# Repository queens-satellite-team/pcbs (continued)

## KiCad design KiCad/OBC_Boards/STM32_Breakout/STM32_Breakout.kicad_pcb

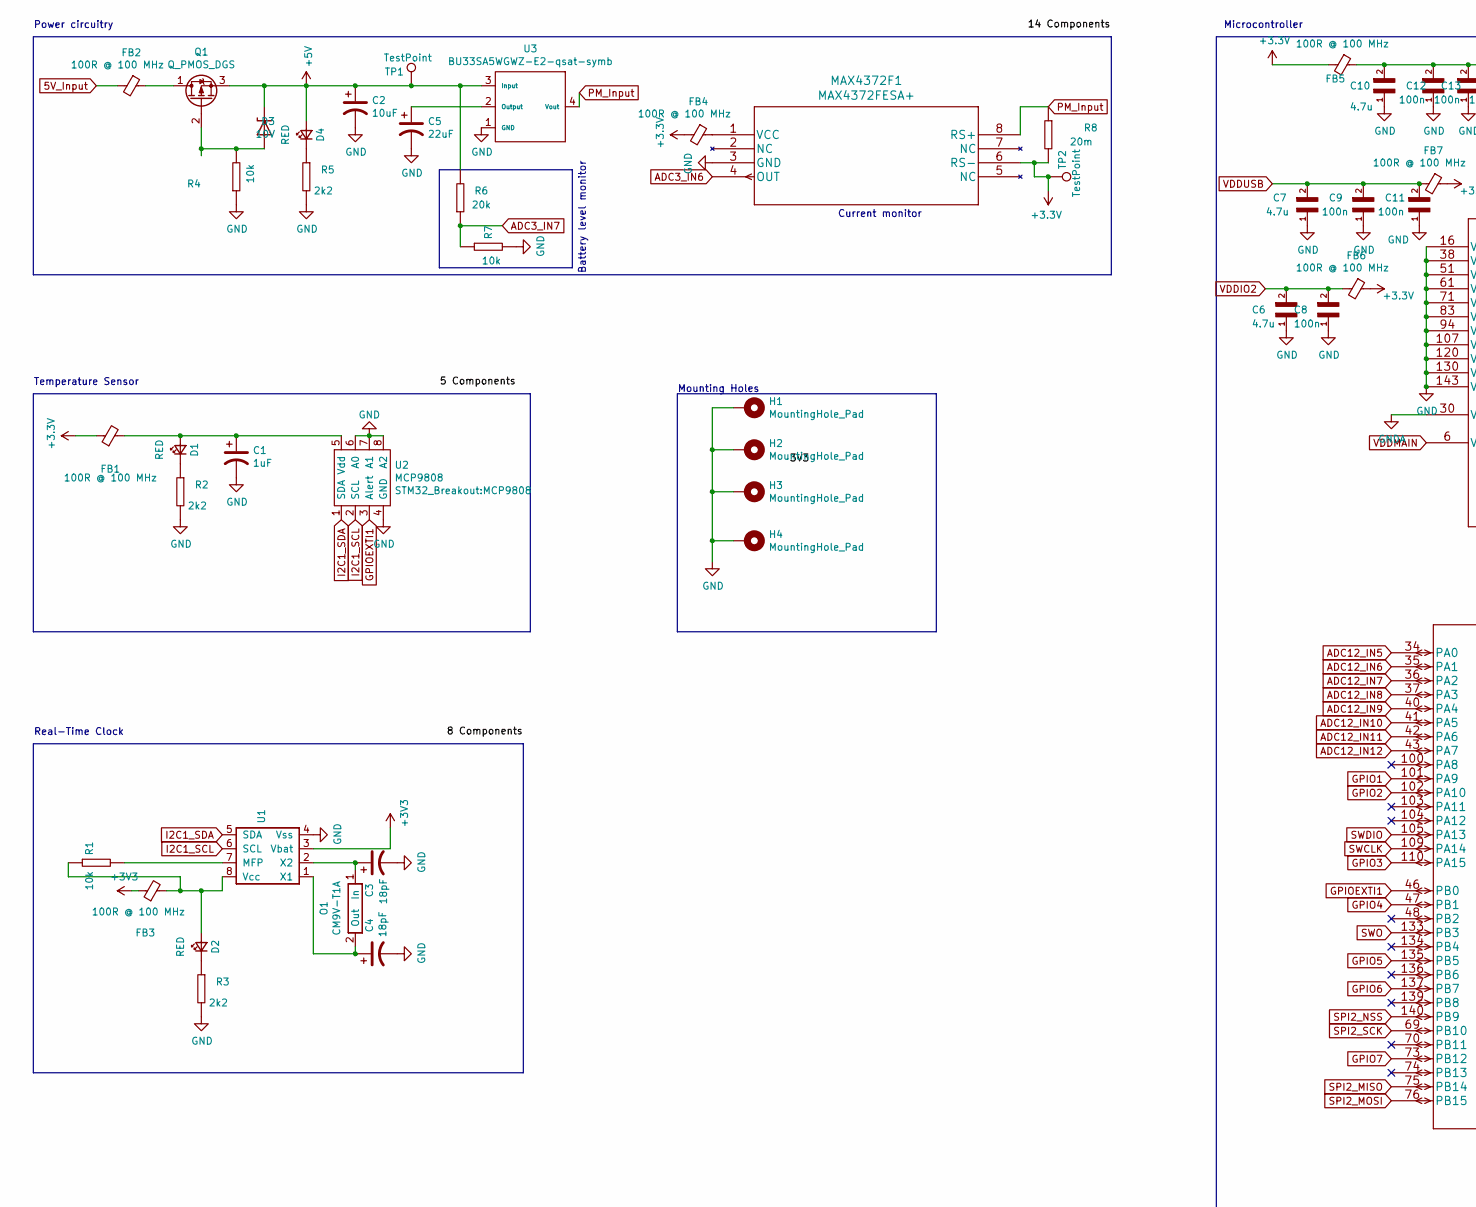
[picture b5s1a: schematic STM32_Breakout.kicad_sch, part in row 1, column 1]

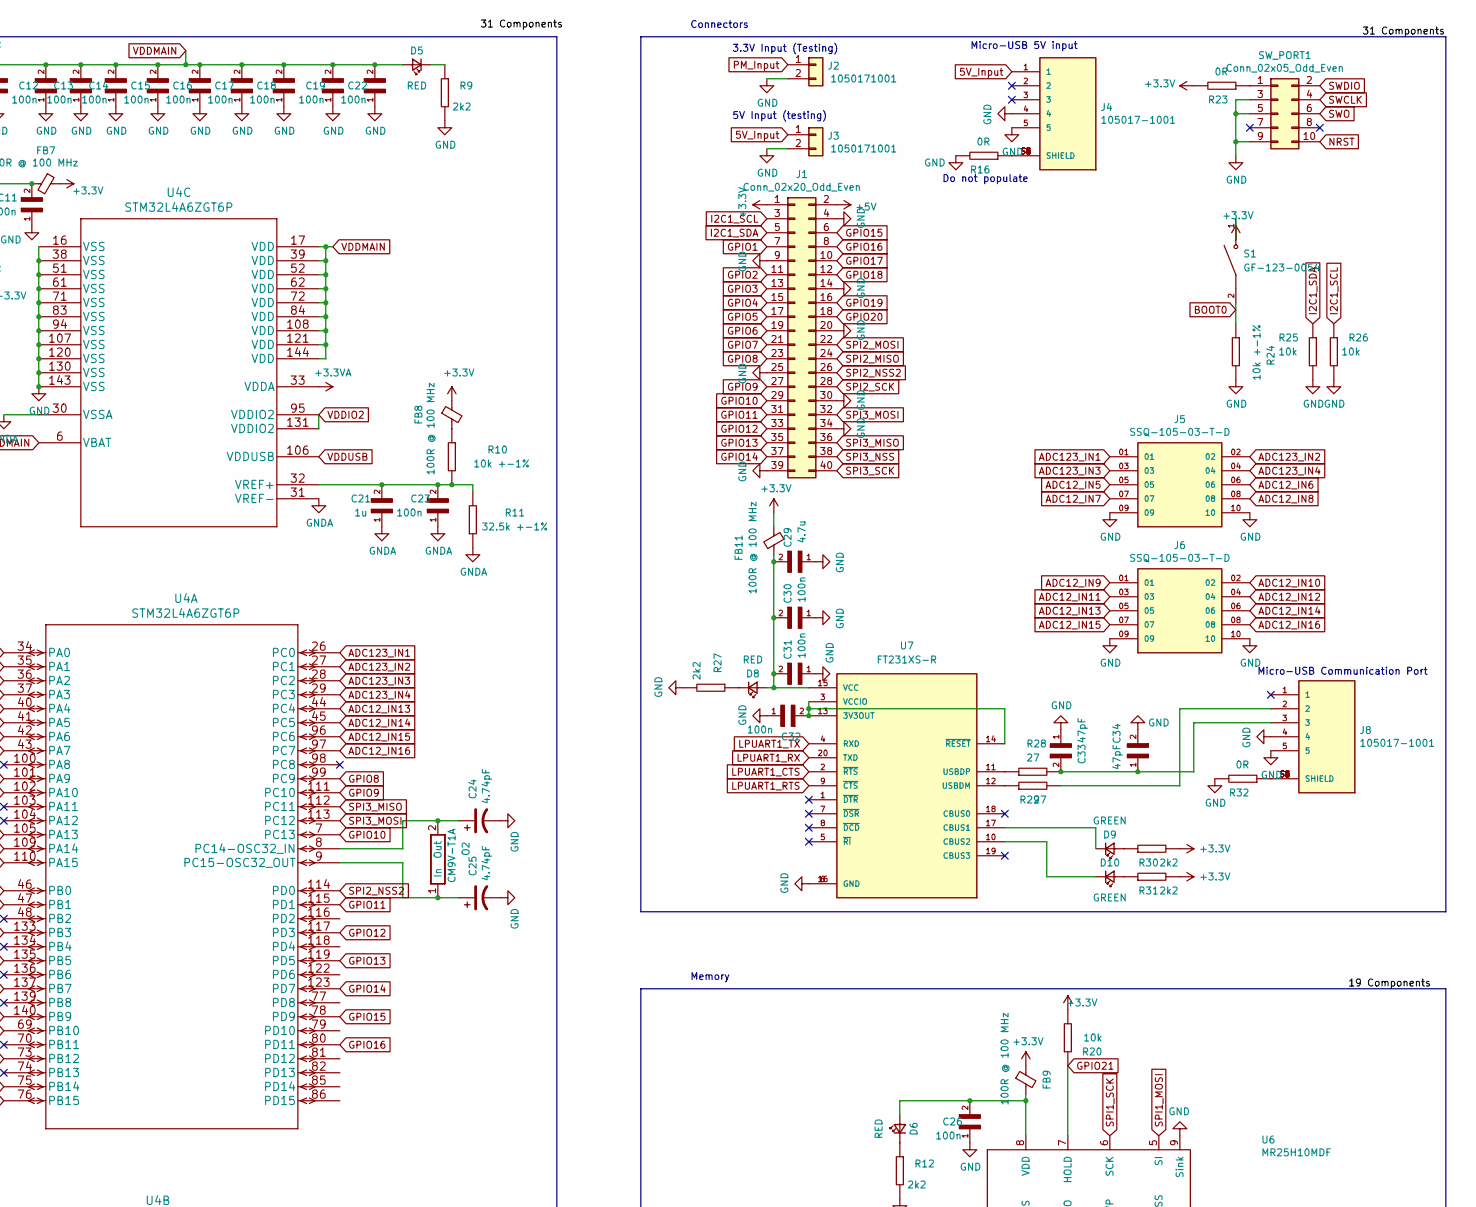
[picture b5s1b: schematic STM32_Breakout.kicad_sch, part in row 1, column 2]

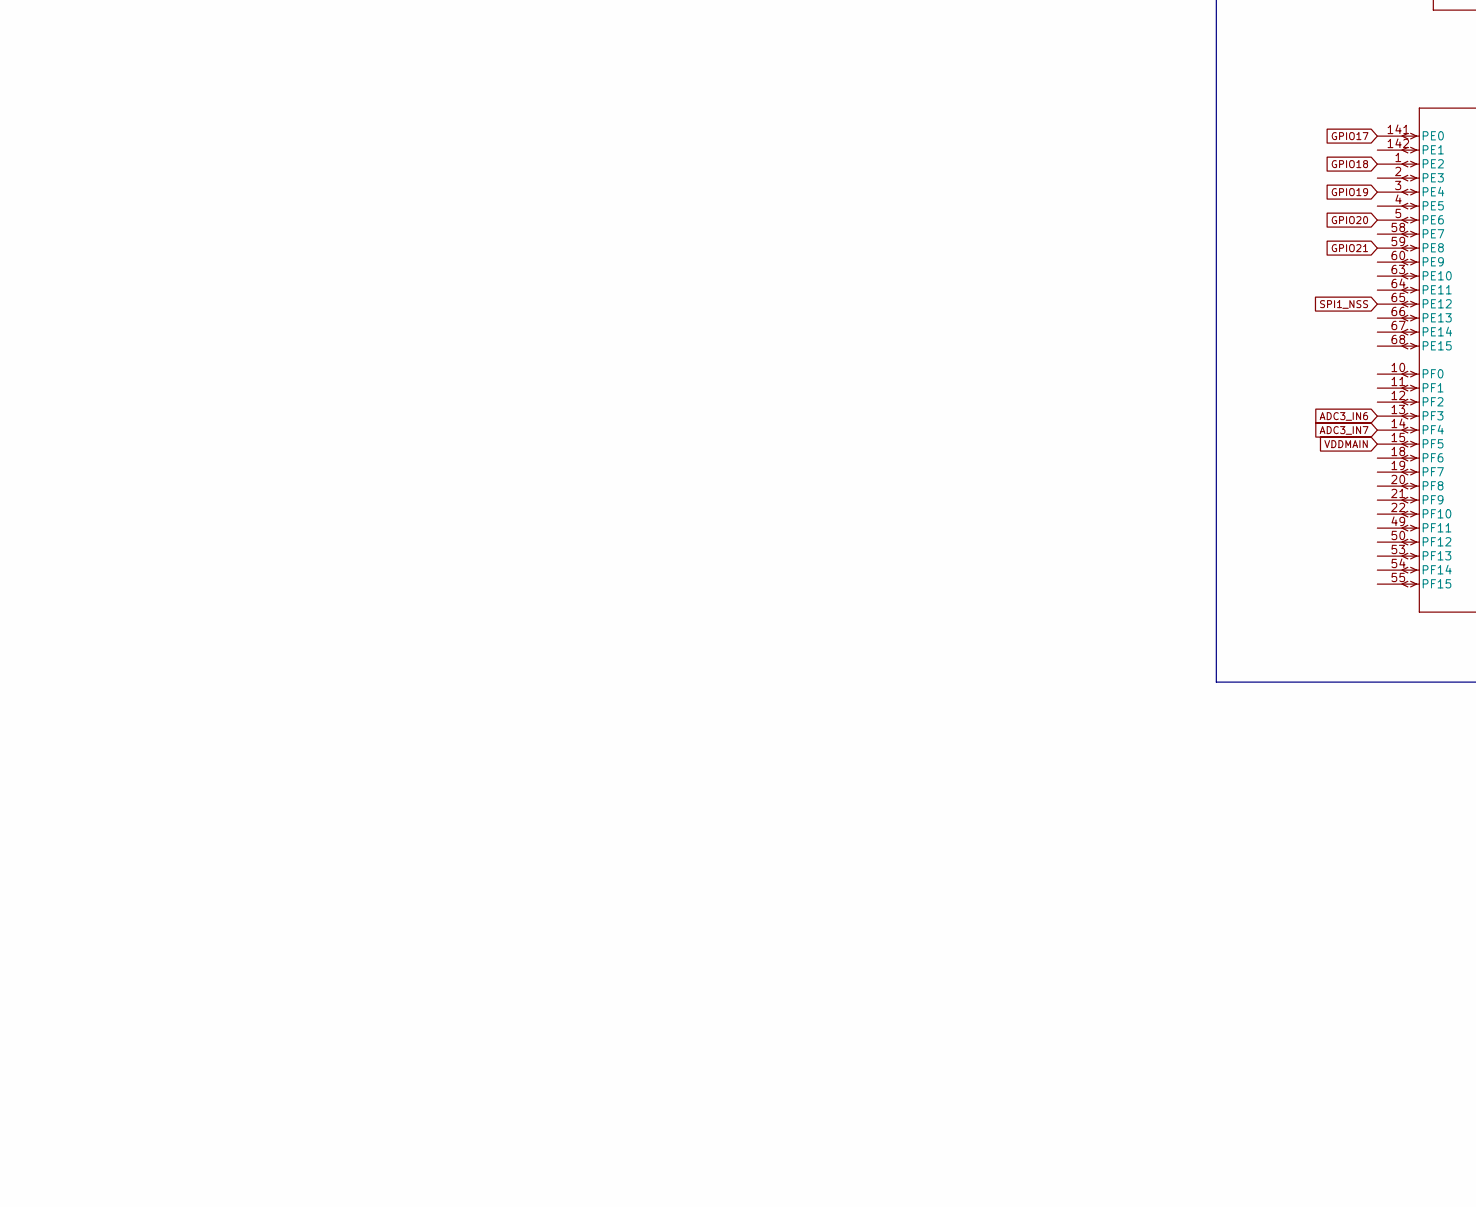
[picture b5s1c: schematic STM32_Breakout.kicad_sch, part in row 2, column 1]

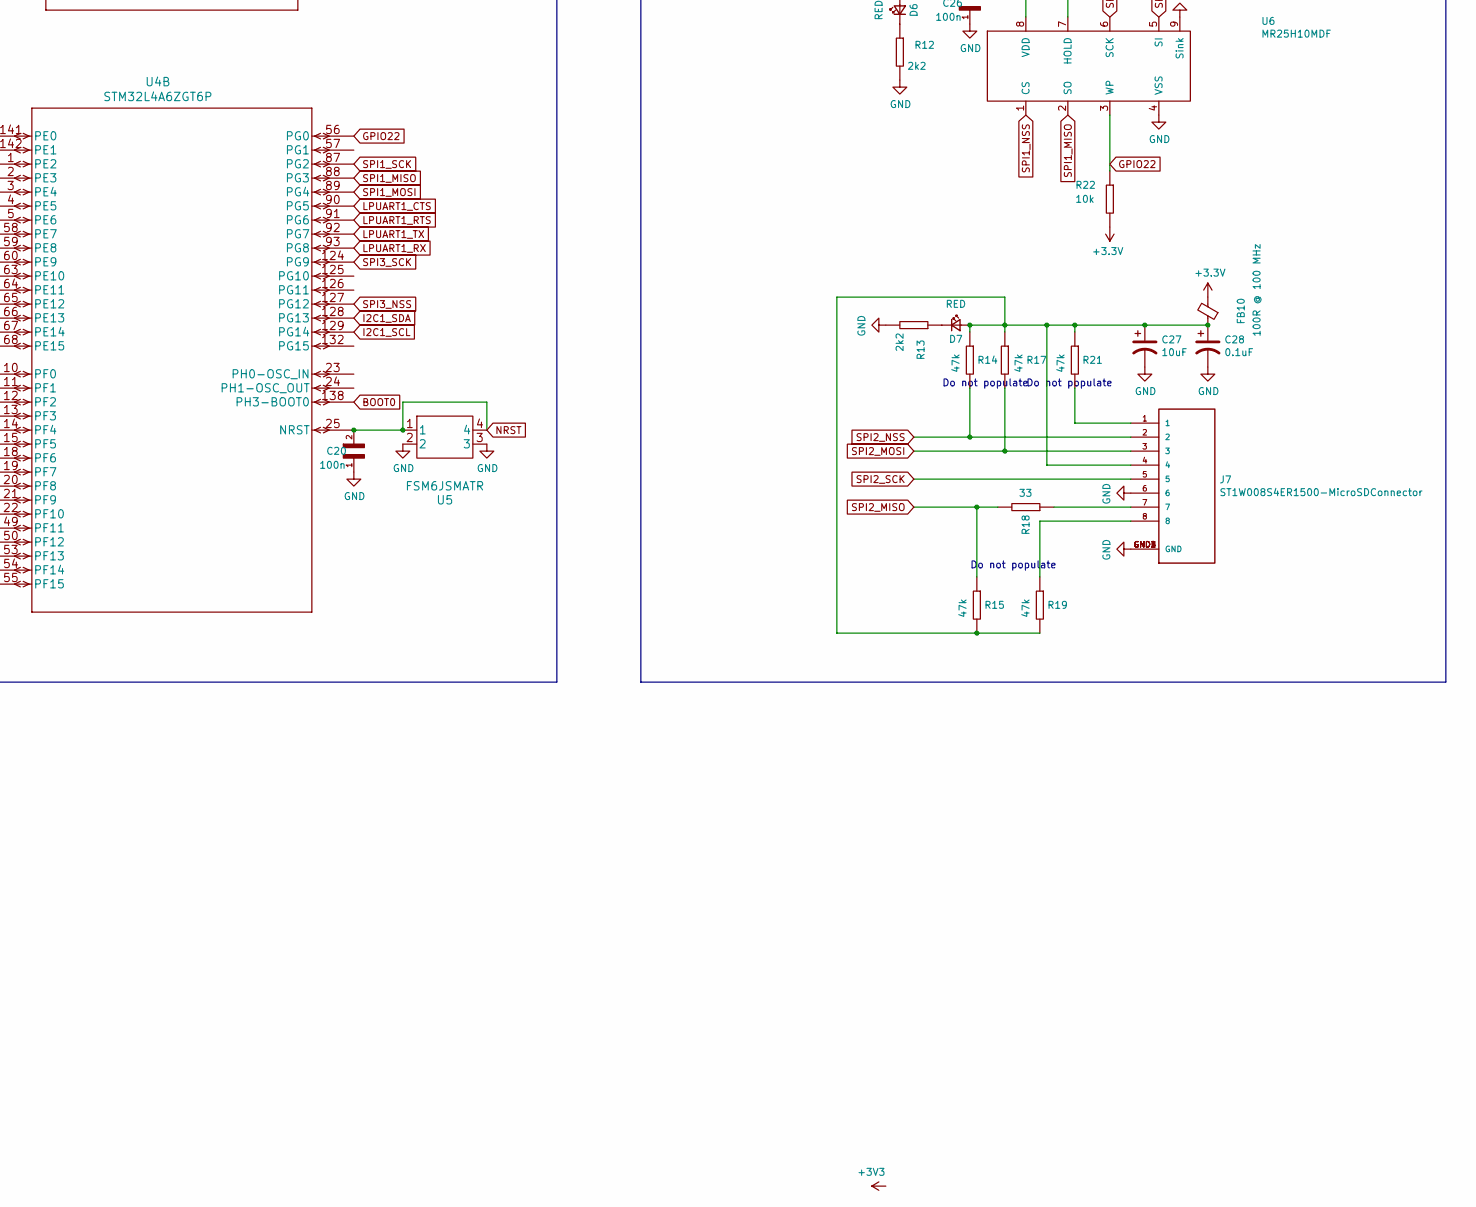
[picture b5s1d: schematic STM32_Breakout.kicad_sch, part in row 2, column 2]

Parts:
C1: 1uF; CAPC1608X90
C2, C27: 10uF; CAPC1608X90
C3, C4: 18pF; CAPC1608X90
C5: 22uF; CAPC1608X90
C6, C7, C10, C29: 4.7u; CAPC1608X90
C8, C9, C11, C12, C13, C14, C15, C16, C17, C18, C19, C20, C22, C23, C26, C30, C31, C32: 100n; CAPC1608X90
C21: 1u; CAPC1608X90
C24, C25: 4.74pF; CAPC1608X90
C28: 0.1uF; CAPC1608X90
C33, C34: 47pF; CAPC1608X90
D1, D2, D4, D5, D6, D7, D8: RED; LED_0603_1608Metric_Pad1.05x0.95mm_HandSolder
D3: 10V; SOT91P240X110-3N
D9, D10: GREEN; LED_0603_1608Metric_Pad1.05x0.95mm_HandSolder
FB1, FB2, FB3, FB4, FB5, FB6, FB7, FB8, FB9, FB10, FB11: 100R @ 100 MHz; INDUC1607X60N
H1, H2, H3, H4: MountingHole_Pad; MountingHole_4.3mm_M4_Pad_Via
J1: Conn_02x20_Odd_Even; PinHeader_2x20_P2.54mm_Vertical
J2, J3: 1050171001; PinHeader_1x02_P2.54mm_Vertical
J4, J8: 105017-1001; MOLEX_105017-1001; PARTREV F
J5, J6: SSQ-105-03-T-D; SAMTEC_SSQ-105-03-T-D; PARTREV R
J7: ST1W008S4ER1500-MicroSDConnector; JAE_ST1W008S4ER1500; PARTREV 2
MAX4372F1: MAX4372FESA+; SOIC127P600X175-8N
O1, O2: CM9V-T1A
Q1: Q_PMOS_DGS; SOT91P240X110-3N
R1, R4, R7, R20, R22, R25, R26: 10k; RESC1607X60N
R2, R3, R5, R9, R12, R13, R27, R30, R31: 2k2; RESC1607X60N
R6: 20k; RESC1607X60N
R8: 20m; RESC1607X60N
R10, R24: 10k +-1%; RESC1607X60N
R11: 32.5k +-1%; RESC1607X60N
R14, R15, R17, R19, R21: 47k; RESC1607X60N
R16, R23, R32: 0R; RESC1607X60N
R18: 33; RESC1607X60N
R28, R29: 27; RESC1607X60N
S1: GF-123-0054; SW_GF-123-0054; PARTREV May 20, 2003
SW_PORT1: Conn_02x05_Odd_Even; PinHeader_2x05_P1.27mm_Vertical_SMD
TP1, TP2: TestPoint; TestPoint_Pad_D2.0mm
U1: MCP7940NT-I_MS; MCP7940NT-I-MS
U2: MCP9808
U3: BU33SA5WGWZ-E2-qsat-symb; BU33SA5WGWZ-E2
U4: STM32L4A6ZGT6P; LQFP144-20x20mm
U5: FSM6JSMATR
U6: MR25H10MDF; SON65P300X300X95-8N
U7: FT231XS-R; SOP63P599X175-20N; PARTREV 1.2

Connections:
5V_Input: FB2.2, J3.1, J4.1
+3.3VA: U4.33 (VDDA)
+5V: C2.1, D3.3 (A), D4.2 (A), J1.2, Q1.3 (S), R6.2, TP1.1, U3.3 (Input)
ADC3_IN6: MAX4372F1.4 (OUT), U4.13 (PF3)
ADC3_IN7: R6.1, R7.1, U4.14 (PF4)
ADC12_IN5: J5.05, U4.34 (PA0)
ADC12_IN6: J5.06, U4.35 (PA1)
ADC12_IN7: J5.07, U4.36 (PA2)
ADC12_IN8: J5.08, U4.37 (PA3)
ADC12_IN9: J6.01, U4.40 (PA4)
ADC12_IN10: J6.02, U4.41 (PA5)
ADC12_IN11: J6.03, U4.42 (PA6)
ADC12_IN12: J6.04, U4.43 (PA7)
ADC12_IN13: J6.05, U4.44 (PC4)
ADC12_IN14: J6.06, U4.45 (PC5)
ADC12_IN15: J6.07, U4.96 (PC6)
ADC12_IN16: J6.08, U4.97 (PC7)
ADC123_IN1: J5.01, U4.26 (PC0)
ADC123_IN2: J5.02, U4.27 (PC1)
ADC123_IN3: J5.03, U4.28 (PC2)
ADC123_IN4: J5.04, U4.29 (PC3)
BOOT0: R24.1, S1.2, U4.138 (PH3-BOOT0)
GND: C1.2, C2.2, C3.2, C4.2, C5.2, C6.1, C7.1, C8.1, C9.1, C10.1, C11.1, C12.1, C13.1, C14.1, C15.1, C16.1, C17.1, C18.1, C19.1, C20.1, C22.1, C24.2, C25.2, C26.1, C27.2, C28.2, C29.1, C30.1, C31.1, C32.1, C33.1, C34.2, H1.1, H2.1, H3.1, H4.1, J1.4, J1.9, J1.14, J1.20, J1.25, J1.30, J1.34, J1.39, J2.2, J3.2, J4.4, J4.5, J5.09, J5.10, J6.09, J6.10, J7.6, J7.GND1 (GND), J7.GND2 (GND), J7.GND3 (GND), J7.GND4 (GND), J8.4, J8.5, MAX4372F1.3 (GND), R2.2, R3.2, R4.1, R5.2, R7.2, R9.2, R12.2, R13.2, R16.2, R24.2, R25.2, R26.2, R27.2, R32.2, SW_PORT1.3, SW_PORT1.5, SW_PORT1.9, U1.4 (Vss), U2.4 (GND), U2.6 (A0), U2.7 (A1), U2.8 (A2), U3.1 (GND), U4.16 (VSS), U4.38 (VSS), U4.51 (VSS), U4.61 (VSS), U4.71 (VSS), U4.83 (VSS), U4.94 (VSS), U4.107 (VSS), U4.120 (VSS), U4.130 (VSS), U4.143 (VSS), U5.2, U5.3, U6.4 (VSS), U6.9 (Sink), U7.6 (GND), U7.16 (GND)
GNDA: C21.1, C23.1, R11.1, U4.30 (VSSA), U4.31 (VREF-)
GPIO1: J1.7, U4.101 (PA9)
GPIO2: J1.11, U4.102 (PA10)
GPIO3: J1.13, U4.110 (PA15)
GPIO4: J1.15, U4.47 (PB1)
GPIO5: J1.17, U4.135 (PB5)
GPIO6: J1.19, U4.137 (PB7)
GPIO7: J1.21, U4.73 (PB12)
GPIO8: J1.23, U4.99 (PC9)
GPIO9: J1.27, U4.111 (PC10)
GPIO10: J1.29, U4.7 (PC13)
GPIO11: J1.31, U4.115 (PD1)
GPIO12: J1.33, U4.117 (PD3)
GPIO13: J1.35, U4.119 (PD5)
GPIO14: J1.37, U4.123 (PD7)
GPIO15: J1.6, U4.78 (PD9)
GPIO16: J1.8, U4.80 (PD11)
GPIO17: J1.10, U4.141 (PE0)
GPIO18: J1.12, U4.1 (PE2)
GPIO19: J1.16, U4.3 (PE4)
GPIO20: J1.18, U4.5 (PE6)
GPIO21: R20.1, U4.59 (PE8), U6.7 (HOLD)
GPIO22: R22.1, U4.56 (PG0), U6.3 (WP)
GPIOEXTI1: U2.3 (Alert), U4.46 (PB0)
I2C1_SCL: J1.3, R26.1, U1.6 (SCL), U2.2 (SCL), U4.129 (PG14)
I2C1_SDA: J1.5, R25.1, U1.5 (SDA), U2.1 (SDA), U4.128 (PG13)
LPUART1_CTS: U4.90 (PG5), U7.2 (~RTS)
LPUART1_RTS: U4.91 (PG6), U7.9 (~CTS)
LPUART1_RX: U4.93 (PG8), U7.20 (TXD)
LPUART1_TX: U4.92 (PG7), U7.4 (RXD)
NRST: C20.2, SW_PORT1.10, U4.25 (NRST), U5.1, U5.4
unnamed: C1.1, D1.2 (A), FB1.2, U2.5 (Vdd)
unnamed: C3.1, O1.1 (In), U1.2 (X2)
unnamed: C4.1, O1.2 (Out), U1.1 (X1)
unnamed: C5.1, U3.2 (Output)
unnamed: C21.2, C23.2, R10.2, R11.2, U4.32 (VREF+)
unnamed: C24.1, O2.2 (Out), U4.8 (PC14-OSC32_IN)
unnamed: C25.1, O2.1 (In), U4.9 (PC15-OSC32_OUT)
unnamed: C26.2, D6.2 (A), FB9.2, U6.8 (VDD)
unnamed: C27.1, C28.1, D7.2 (A), FB10.1, J7.4, R14.1, R15.2, R17.1, R19.2, R21.1
unnamed: C29.2, C30.2, C31.2, D8.2 (A), FB11.2, U7.15 (VCC)
unnamed: C32.2, U7.3 (VCCIO), U7.13 (3V3OUT), U7.14 (~RESET)
unnamed: C33.2, C34.1, J8.3, R28.2
unnamed: D1.1 (K), R2.1
unnamed: D2.1 (K), R3.1
unnamed: D2.2 (A), FB3.2, R1.1, U1.8 (Vcc)
unnamed: D4.1 (K), R5.1
unnamed: D5.1 (K), R9.1
unnamed: D6.1 (K), R12.1
unnamed: D7.1 (K), R13.1
unnamed: D8.1 (K), R27.1
unnamed: D9.1 (K), U7.17 (CBUS1)
unnamed: D9.2 (A), R30.1
unnamed: D10.1 (K), U7.10 (CBUS2)
unnamed: D10.2 (A), R31.1
unnamed: FB2.1, Q1.1 (D)
unnamed: FB4.1, MAX4372F1.1 (VCC)
unnamed: FB8.2, R10.1
unnamed: J4.S1 (SHIELD), J4.S2 (SHIELD), J4.S3 (SHIELD), J4.S4 (SHIELD), J4.S5 (SHIELD), J4.S6 (SHIELD), R16.1
unnamed: J7.1, R21.2
unnamed: J7.7, R18.1
unnamed: J7.8, R19.1
unnamed: J8.2, R29.2
unnamed: J8.S1 (SHIELD), J8.S2 (SHIELD), J8.S3 (SHIELD), J8.S4 (SHIELD), J8.S5 (SHIELD), J8.S6 (SHIELD), R32.1
unnamed: D3.1 (K), Q1.2 (G), R4.2
unnamed: R1.2, U1.7 (MFP)
unnamed: R23.1, SW_PORT1.1
unnamed: R28.1, U7.11 (USBDP)
unnamed: R29.1, U7.12 (USBDM)
PM_Input: J2.1, MAX4372F1.8 (RS+), R8.1, U3.4 (Vout)
SPI1_MISO: U4.88 (PG3), U6.2 (SO)
SPI1_MOSI: U4.89 (PG4), U6.5 (SI)
SPI1_NSS: U4.65 (PE12), U6.1 (CS)
SPI1_SCK: U4.87 (PG2), U6.6 (SCK)
SPI2_MISO: J1.24, R15.1, R18.2, U4.75 (PB14)
SPI2_MOSI: J1.22, J7.3, R17.2, U4.76 (PB15)
SPI2_NSS: J7.2, R14.2, U4.140 (PB9)
SPI2_NSS2: J1.26, U4.114 (PD0)
SPI2_SCK: J1.28, J7.5, U4.69 (PB10)
SPI3_MISO: J1.36, U4.112 (PC11)
SPI3_MOSI: J1.32, U4.113 (PC12)
SPI3_NSS: J1.38, U4.127 (PG12)
SPI3_SCK: J1.40, U4.124 (PG9)
SWCLK: SW_PORT1.4, U4.109 (PA14)
SWDIO: SW_PORT1.2, U4.105 (PA13)
SWO: SW_PORT1.6, U4.133 (PB3)
VDDIO2: C6.2, C8.2, FB6.2, U4.95 (VDDIO2), U4.131 (VDDIO2)
VDDMAIN: C10.2, C12.2, C13.2, C14.2, C15.2, C16.2, C17.2, C18.2, C19.2, C22.2, D5.2 (A), FB5.1, U4.6 (VBAT), U4.15 (PF5), U4.17 (VDD), U4.39 (VDD), U4.52 (VDD), U4.62 (VDD), U4.72 (VDD), U4.84 (VDD), U4.108 (VDD), U4.121 (VDD), U4.144 (VDD)
VDDUSB: C7.2, C9.2, C11.2, FB7.2, U4.106 (VDDUSB)

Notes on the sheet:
Current monitor
Power circuitry
Mounting Holes
Memory
Do not populate
3.3V Input (Testing)
5V Input (testing)
Connectors
Real-Time Clock
Temperature Sensor
Micro-USB Communication Port
Battery level monitor
Microcontroller
Micro-USB 5V input

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
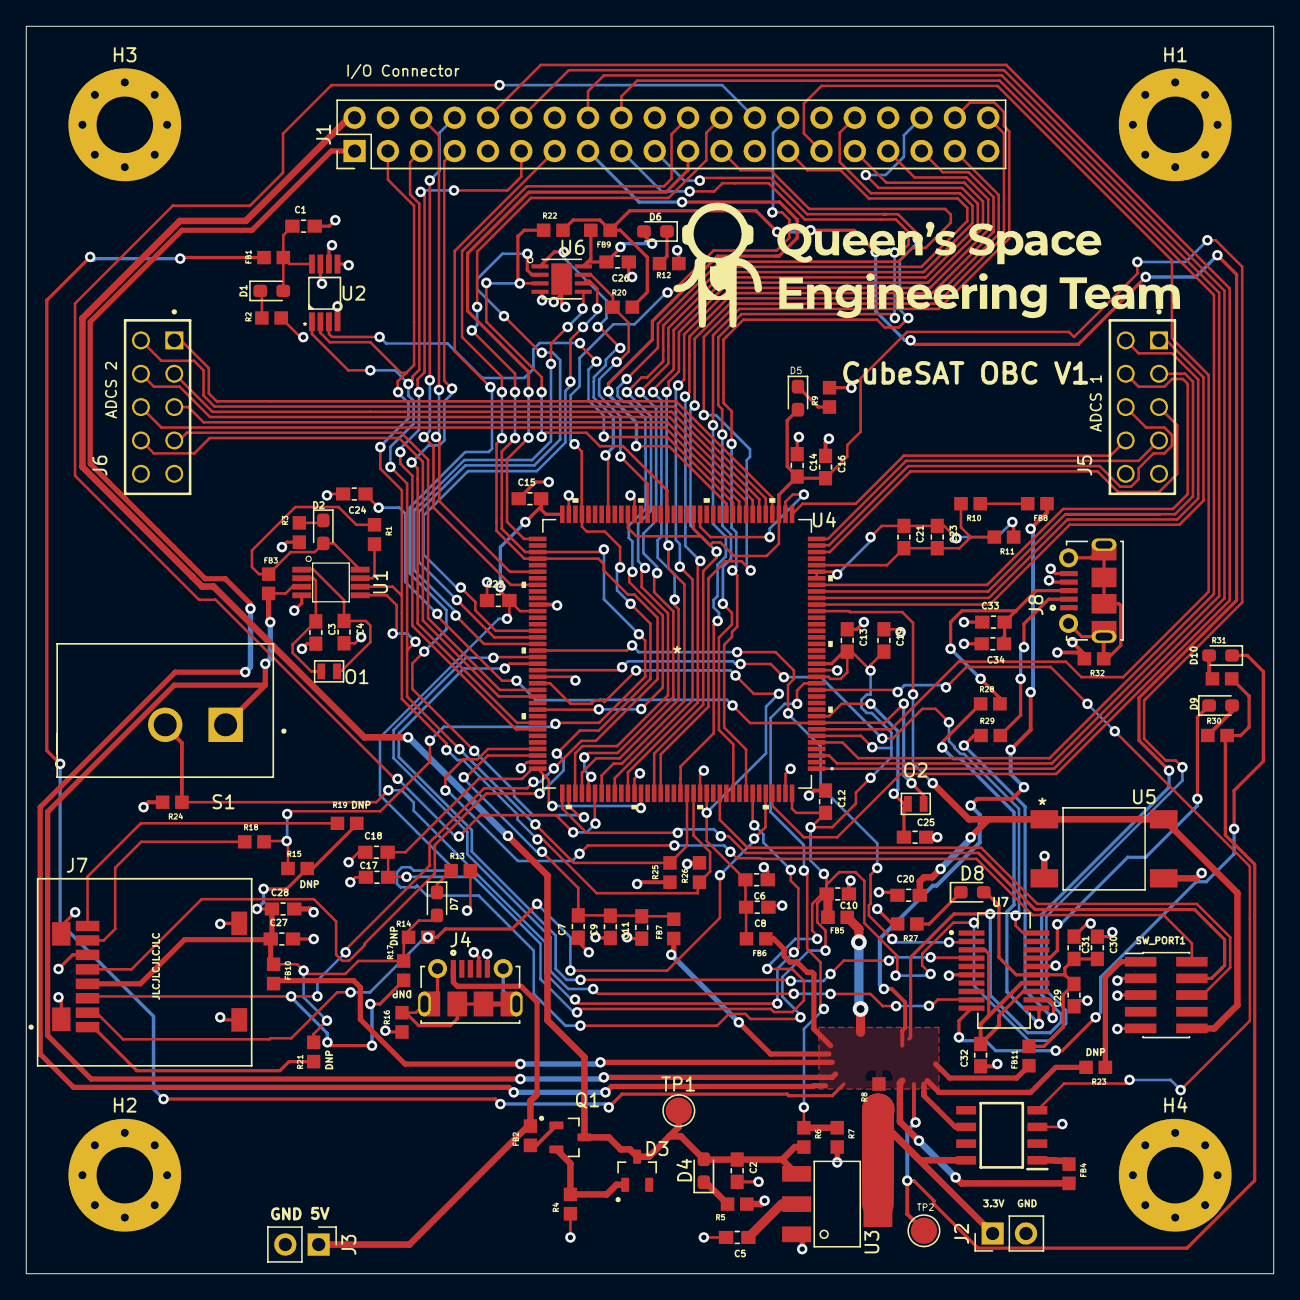
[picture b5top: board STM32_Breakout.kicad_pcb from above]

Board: 4 copper layers, 95.0 x 95.0 mm, 114 parts (0 on the bottom side), 112 nets.

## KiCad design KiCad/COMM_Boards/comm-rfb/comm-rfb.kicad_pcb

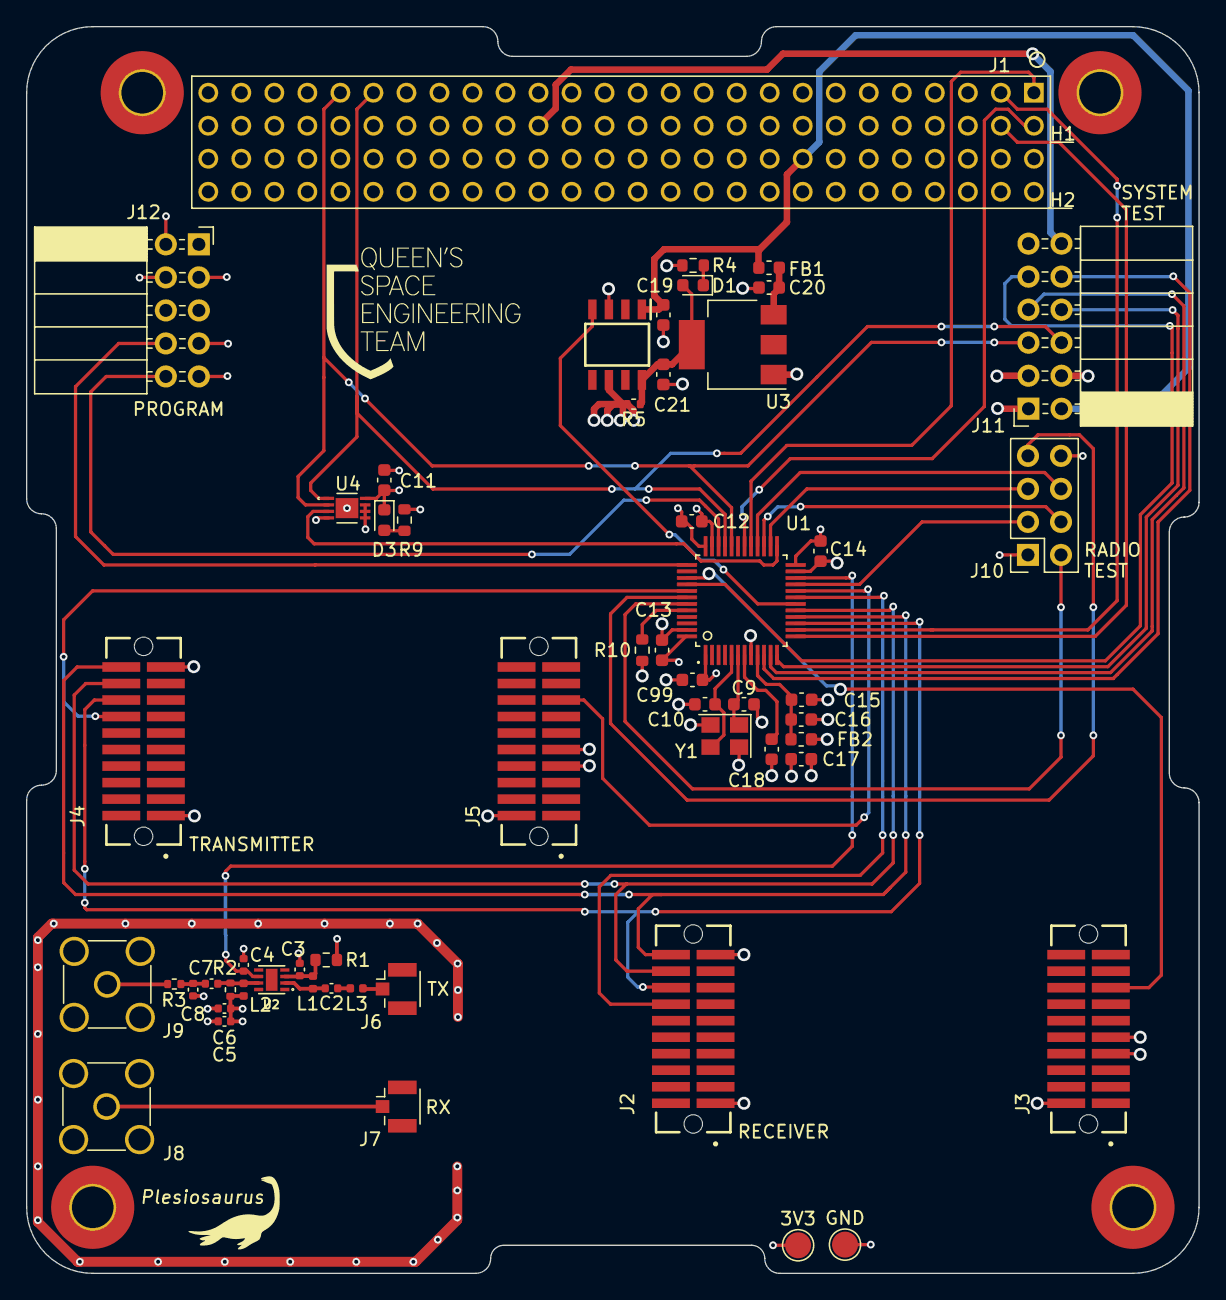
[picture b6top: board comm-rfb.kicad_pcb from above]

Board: 4 copper layers, 90.2 x 95.9 mm, 59 parts (0 on the bottom side), 49 nets.

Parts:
C2: 20p; C_0402_1005Metric
C3, C4, C5: 1000p; C_0402_1005Metric
C6, C7: 10p; C_0402_1005Metric
C8: 1p8; C_0402_1005Metric
C9, C10: 10p; C_0603_1608Metric
C11: 0.1uF; C_0603_1608Metric
C12, C13, C14, C19, C99: 100n; C_0603_1608Metric
C15: 10n; C_0603_1608Metric
C16, C17: 1u; C_0603_1608Metric
C18: 100u; C_0603_1608Metric
C20, C21: 22u; C_0603_1608Metric
D1: LED; LED_0603_1608Metric
D3: RED; D_0603_1608Metric
FB1: 100R @ 100 MHz; L_0603_1608Metric
FB2: 100R @ 100MHz; L_0603_1608Metric
H1, H2, H3, H4: MountingHole_Pad; MountingHole_3.2mm_M3_Pad_TopBottom
J1: PC104_Connector; pc104-connector
J2, J3, J4, J5: TFM-110-02-SM-D-A-K-TR; SAMTEC_TFM-110-02-SM-D-A-K-TR
J6, J7: Conn_Coaxial; U.FL_Hirose_U.FL-R-SMT-1_Vertical
J8, J9: Conn_Coaxial; SMA_Amphenol_132134-11_Vertical
J10: Radio Test Connector; PinSocket_2x04_P2.54mm_Vertical
J11: System Test Connector; PinSocket_2x06_P2.54mm_Horizontal
J12: Programming Header; PinSocket_2x05_P2.54mm_Horizontal
L1: 150n; L_0402_1005Metric
L2: 22n; L_0402_1005Metric
L3: 12n; L_0402_1005Metric
MAX4372F1: MAX4372FESA+; SOIC127P600X175-8N
R1: 9.1k; R_0603_1608Metric
R2: 330; R_0402_1005Metric
R3: 15; R_0402_1005Metric
R4: 1k5; R_0603_1608Metric
R5: 100m; R_0402_1005Metric
R9: 2.2k; R_0603_1608Metric
R10: 10k; R_0603_1608Metric
TP1: 3V3; TestPoint_Pad_D2.0mm
TP2: GND; TestPoint_Pad_D2.0mm
U1: STM32F030CCT6; QFP50P900X900X160-48N
U2: SKY67150-396LF; SON50P200X200X80-9N
U3: AMS1117-3.3; SOT-223-3_TabPin2
U4: MCP9808T-E/MC; MCP9808T-E&slash_MC
Y1: 16 MHz; Crystal_SMD_3225-4Pin_3.2x2.5mm

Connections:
5V0-CHG: J1.32 (H1-32), J11.12
+3.3VA: C15.1, C16.1, FB2.1, U1.9 (VDDA)
+3V3: C5.1, C6.1, C11.1, C12.1, C13.1, C14.1, C17.1, C99.1, D3.1 (A), FB2.2, J3.07, J3.09, J5.07, J5.09, J10.8, J11.1, J12.4, J12.7, L2.1, MAX4372F1.6 (RS-), R1.1, R2.1, R5.2, TP1.1, U1.1 (VDD), U1.24 (VDD), U1.36 (VDD), U1.48 (VDD), U4.8 (VDD)
/BOOT0: R10.1, U1.44 (BOOT0)
/NRST: C18.1, U1.7 (~NRST)
/RF Front End (Tx & Rx)/AMP-TO-EXT: J9.1 (In), R3.2
/RF Front End (Tx & Rx)/EM-TO-AMP: J6.1 (In), L3.1
/RF Front End (Tx & Rx)/RX-TO-EM: J7.1 (In), J8.1 (In)
AMP-ENABLE: C4.1, U1.22 (PB11), U2.6 (~ENABLE)
COMM-CTS: J1.3 (H1-3), U1.14 (PA4)
COMM-RTS: J1.4 (H1-4), U1.13 (PA3)
COMM-RXD: J1.2 (H1-2), U1.30 (PA9)
COMM-TXD: J1.1 (H1-1), U1.29 (PA8)
CURR-MONITOR: MAX4372F1.4 (OUT), U1.18 (PB0)
GND: C3.2, C4.2, C5.2, C6.2, C8.2, C9.2, C10.2, C11.2, C12.2, C13.2, C14.2, C15.2, C16.2, C17.2, C18.2, C19.2, C20.2, C21.2, C99.2, J1.61 (H2-9), J1.66 (H1-14), J1.69 (H2-17), J1.72 (H1-20), J1.73 (H2-21), J1.74 (H1-22), J1.81 (H2-29), J1.82 (H1-30), J1.84 (H1-32), J2.01, J2.19, J3.02, J4.01, J4.19, J5.02, J6.2 (Ext), J7.2 (Ext), J8.2 (Ext), J9.2 (Ext), J10.1, J11.3, J11.4, J11.11, J12.2, J12.3, J12.9, MAX4372F1.3 (GND), R4.1, R9.2, R10.2, TP2.1, U1.8 (VSSA), U1.23 (VSS), U1.35 (VSS), U1.47 (VSS), U3.1 (GND), U4.4 (GND), U4.5 (A2), U4.6 (A1), U4.7 (A0), U4.9 (EPAD), Y1.2, Y1.4
I2C2-SCK: J1.43 (H1-43), J11.5, U1.32 (PA11), U4.2 (SCL)
I2C2-SDA: J1.41 (H1-41), J11.6, U1.33 (PA12), U4.1 (SDA)
unnamed: C2.1, L3.2
unnamed: C2.2, L1.1, U2.2 (RFIN)
unnamed: C3.1, L1.2, R1.2, U2.3 (VBIAS)
unnamed: C7.1, L2.2, R2.2, U2.7 (RFOUT/VDD)
unnamed: C7.2, C8.1, R3.1
unnamed: C20.1, FB1.1, U3.3 (VI)
unnamed: D1.1 (K), R4.2
unnamed: D3.2 (K), R9.1
RESET-RX: J3.15, U1.39 (PB3)
RESET-TX: J5.15, U1.20 (PB2)
SPI1-CSN-RX: J2.14, U1.19 (PB1)
SPI1-CSN-TX: J4.14, U1.41 (PB5)
SPI1-MISO: J2.20, J4.20, U1.16 (PA6)
SPI1-MOSI: J2.18, J4.18, U1.17 (PA7)
SPI1-SCLK: J2.16, J4.16, U1.15 (PA5)
SPI2-CE: J10.2, U1.43 (PB7)
SPI2-CSN: J10.7, U1.42 (PB6)
SPI2-IRQ: J10.5, U1.26 (PB13)
SPI2-MISO: J10.4, U1.27 (PB14)
SPI2-MOSI: J10.6, U1.28 (PB15)
SPI2-SCLK: J10.3, U1.21 (PB10)
SW6-5V: C19.1, FB1.2, J1.67 (H2-15), J11.2, MAX4372F1.1 (VCC)
SWCLK: J12.8, U1.37 (PA14(SWCLK))
SWDIO: J12.10, U1.34 (PA13(SWDIO))
SYS-GPIO1: J11.10, U1.10 (PA0)
SYS-GPIO2: J11.7, U1.11 (PA1)
SYS-GPIO3: J11.8, U1.12 (PA2)
SYS-GPIO4: J11.9, U1.40 (PB4)
TEMP-ALERT: U1.25 (PB12), U4.3 (ALERT)
VCC_3V3: C21.1, D1.2 (A), MAX4372F1.8 (RS+), R5.1, U3.2 (VO)
XOSC_IN: C10.1, U1.5 (PF0(OSC_IN)), Y1.3
XOSC_OUT: C9.1, U1.6 (PF1(OSC_OUT)), Y1.1

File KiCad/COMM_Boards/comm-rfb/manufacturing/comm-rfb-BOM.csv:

Comment,Designator,Footprint,LCSC Part Number
0.1uF,C11,Capacitor_SMD:C_0603_1608Metric,C105907
100n,"C12,C13,C14,C19,C99",Capacitor_SMD:C_0603_1608Metric,C105907
10n,C15,Capacitor_SMD:C_0603_1608Metric,C385970
1u,"C16,C17",Capacitor_SMD:C_0603_1608Metric,C167338
10u,C18,Capacitor_SMD:C_0603_1608Metric,C91150
20p,C2,Capacitor_SMD:C_0402_1005Metric,C107000
22u,"C20,C21",Capacitor_SMD:C_0603_1608Metric,C87153
1000p,"C3,C4,C5",Capacitor_SMD:C_0402_1005Metric,C106205
10p,"C6,C7",Capacitor_SMD:C_0402_1005Metric,C650948
1p8,C8,Capacitor_SMD:C_0402_1005Metric,C76903
10p,"C9,C10",Capacitor_SMD:C_0603_1608Metric,C56033
LED BLUE,D1,LED_SMD:LED_0603_1608Metric,C2837377
LED BLUE,D3,Diode_SMD:D_0603_1608Metric,C2837377
100R @ 100 MHz,FB1,Inductor_SMD:L_0603_1608Metric,C96995
100R @ 100MHz,FB2,Inductor_SMD:L_0603_1608Metric,C96995
Conn_Coaxial,"J6,J7",Connector_Coaxial:U.FL_Hirose_U.FL-R-SMT-1_Vertical,C88373
Conn_Coaxial,"J8,J9",Connector_Coaxial:SMA_Amphenol_132134-11_Vertical,C2693814
150n,L1,Inductor_SMD:L_0402_1005Metric,C162548
22n,L2,Inductor_SMD:L_0402_1005Metric,C142243
12n,L3,Inductor_SMD:L_0402_1005Metric,C86128
9.1k,R1,Resistor_SMD:R_0603_1608Metric,C101399
10k,R10,Resistor_SMD:R_0603_1608Metric,C269701
330,R2,Resistor_SMD:R_0402_1005Metric,C156103
15,R3,Resistor_SMD:R_0402_1005Metric,C208806
1k5,R4,Resistor_SMD:R_0603_1608Metric,C114668
100m,R5,Resistor_SMD:R_0402_1005Metric,C724023
2.2k,R9,Resistor_SMD:R_0603_1608Metric,C116387
STM32F030CCT6,U1,qset-footprints:QFP50P900X900X160-48N,C81787
AMS1117-3.3,U3,Package_TO_SOT_SMD:SOT-223-3_TabPin2,C110474
16 MHz,Y1,Crystal:Crystal_SMD_3225-4Pin_3.2x2.5mm,C251610

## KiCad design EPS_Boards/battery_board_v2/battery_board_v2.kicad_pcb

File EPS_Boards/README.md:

EPS Printed Circuit Boards

**Note:** For the Solar Panel RevA, this file was made in KiCad 7.0 and can not be opened with earlier KiCad versions. 

|Board Name|Description|Status|Dinosaur Nickname|
|-|-|-|-|
|Solar Panel RevA| Supplies power generation capabilities for the satellite. Current PCB design is a smaller ~1U version to be used for testing. | Fabricated | TBD |
|Battery Board| Supplies power storage capabilites for the satellite. Contains voltage and current protections at the cell and system level. | In Progress | TBD |

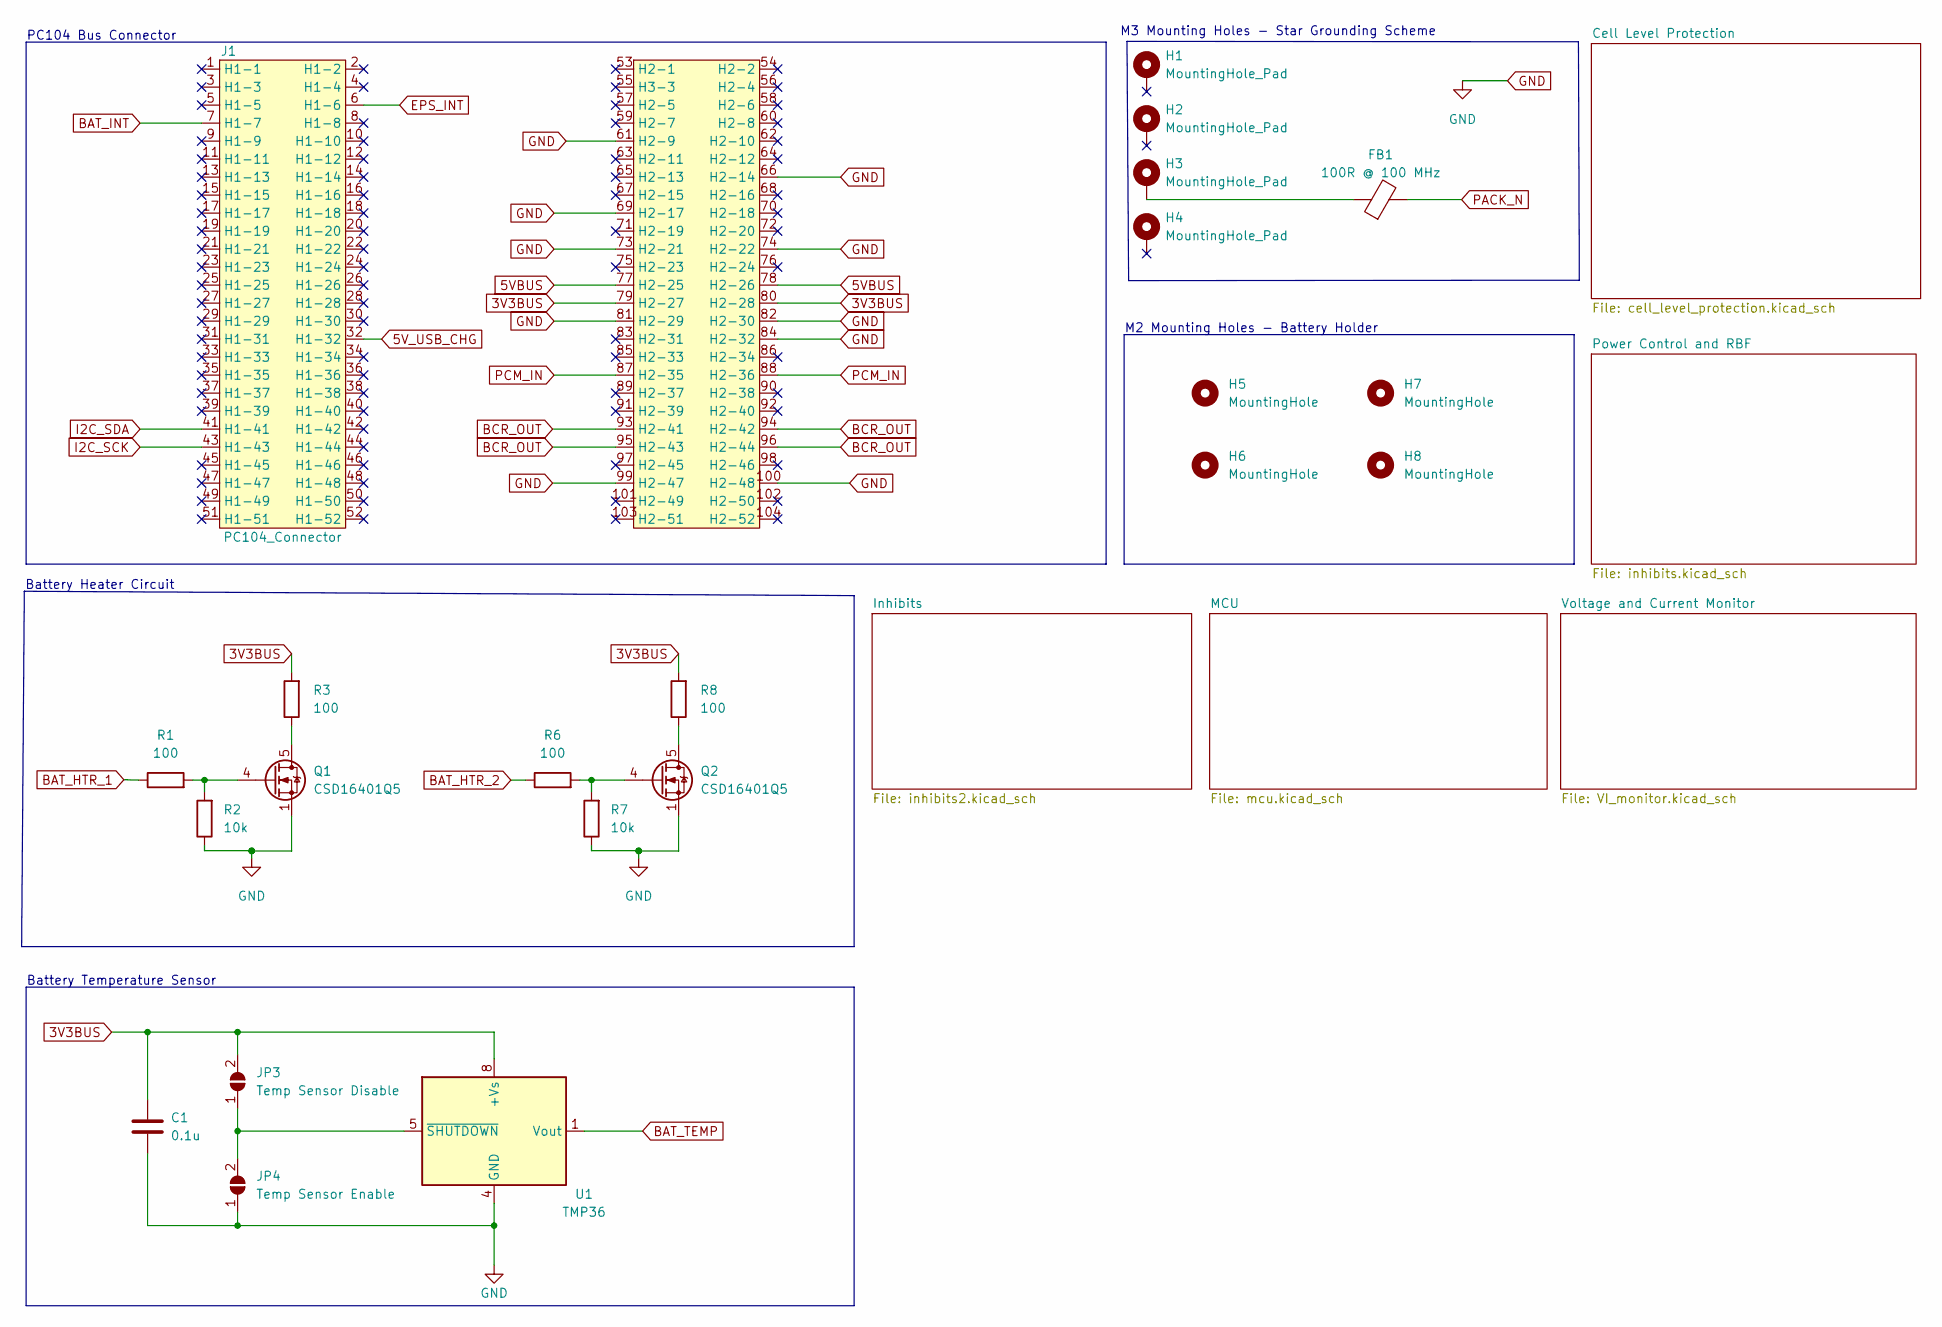
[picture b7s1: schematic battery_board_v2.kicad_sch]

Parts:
C1: 0.1u; C_0402_1005Metric
FB1: 100R @ 100 MHz; L_0603_1608Metric
H1, H2, H3, H4: MountingHole_Pad; MountingHole_3.2mm_M3_Pad_TopBottom
H5, H6, H7, H8: MountingHole; MountingHole_2.2mm_M2_DIN965_Pad
J1: PC104_Connector; pc104-connector
JP3: Temp Sensor Disable; SolderJumper-2_P1.3mm_Open_Pad1.0x1.5mm
JP4: Temp Sensor Enable; SolderJumper-2_P1.3mm_Open_Pad1.0x1.5mm
Q1, Q2: CSD16401Q5; TDSON-8-1
R1, R6: 100; R_0402_1005Metric
R2, R7: 10k; R_0402_1005Metric
R3, R8: 100; R_Axial_DIN0207_L6.3mm_D2.5mm_P7.62mm_Horizontal
U1: TMP36; SOIC-8_3.9x4.9mm_P1.27mm

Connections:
3V3BUS: C1.1, J1.79 (H2-27), J1.80 (H2-28), JP3.2 (B), R3.2, R8.2, U1.8 (+Vs); also elsewhere on the board
5VBUS: J1.77 (H2-25), J1.78 (H2-26)
5V_USB_CHG: J1.32 (H1-32)
BAT_HTR_1: R1.1; also elsewhere on the board
BAT_HTR_2: R6.1; also elsewhere on the board
BAT_INT: J1.7 (H1-7); also elsewhere on the board
BAT_TEMP: U1.1 (Vout); also elsewhere on the board
BCR_OUT: J1.93 (H2-41), J1.94 (H2-42), J1.95 (H2-43), J1.96 (H2-44); also elsewhere on the board
EPS_INT: J1.6 (H1-6); also elsewhere on the board
GND: C1.2, J1.61 (H2-9), J1.66 (H2-14), J1.69 (H2-17), J1.73 (H2-21), J1.74 (H2-22), J1.81 (H2-29), J1.82 (H2-30), J1.84 (H2-32), J1.99 (H2-47), J1.100 (H2-48), JP4.1 (A), Q1.1 (S), Q1.2 (S), Q1.3 (S), Q2.1 (S), Q2.2 (S), Q2.3 (S), R2.1, R7.1, U1.4 (GND); also elsewhere on the board
I2C_SCK: J1.43 (H1-43); also elsewhere on the board
I2C_SDA: J1.41 (H1-41); also elsewhere on the board
unnamed: FB1.1, H3.1
unnamed: JP3.1 (A), JP4.2 (B), U1.5 (~SHUTDOWN)
unnamed: Q1.4 (G), R1.2, R2.2
unnamed: Q1.5 (D), R3.1
unnamed: Q2.4 (G), R6.2, R7.2
unnamed: Q2.5 (D), R8.1
PACK_N: FB1.2; also elsewhere on the board
PCM_IN: J1.87 (H2-35), J1.88 (H2-36); also elsewhere on the board

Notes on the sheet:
M2 Mounting Holes - Battery Holder
Battery Temperature Sensor
Battery Heater Circuit
PC104 Bus Connector
M3 Mounting Holes - Star Grounding Scheme
